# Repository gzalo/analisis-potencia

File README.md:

# Ataque a implementación embebida de AES-128 aplicando Analisis de Correlación de Potencia

Por Gonzalo Avila Alterach ([gzalo.com](https://gzalo.com))

Trabajo presentado en el SASE 2017: [Poster resumen](https://drive.google.com/file/d/0B66P5yRqMPOtamxIRzJjNnZKbFN4UW5kdmpBaS1vaHlMY0hv/view?usp=sharing&resourcekey=0-a8aOC6rB0S7HgKkPsgE3aA) y [Paper (en la página 176)](https://drive.google.com/file/d/0B66P5yRqMPOtMDNuS2NmNnpoXzQ/view?usp=sharing&resourcekey=0-7ZjvjVjSThMPrzhqmmbE-w)

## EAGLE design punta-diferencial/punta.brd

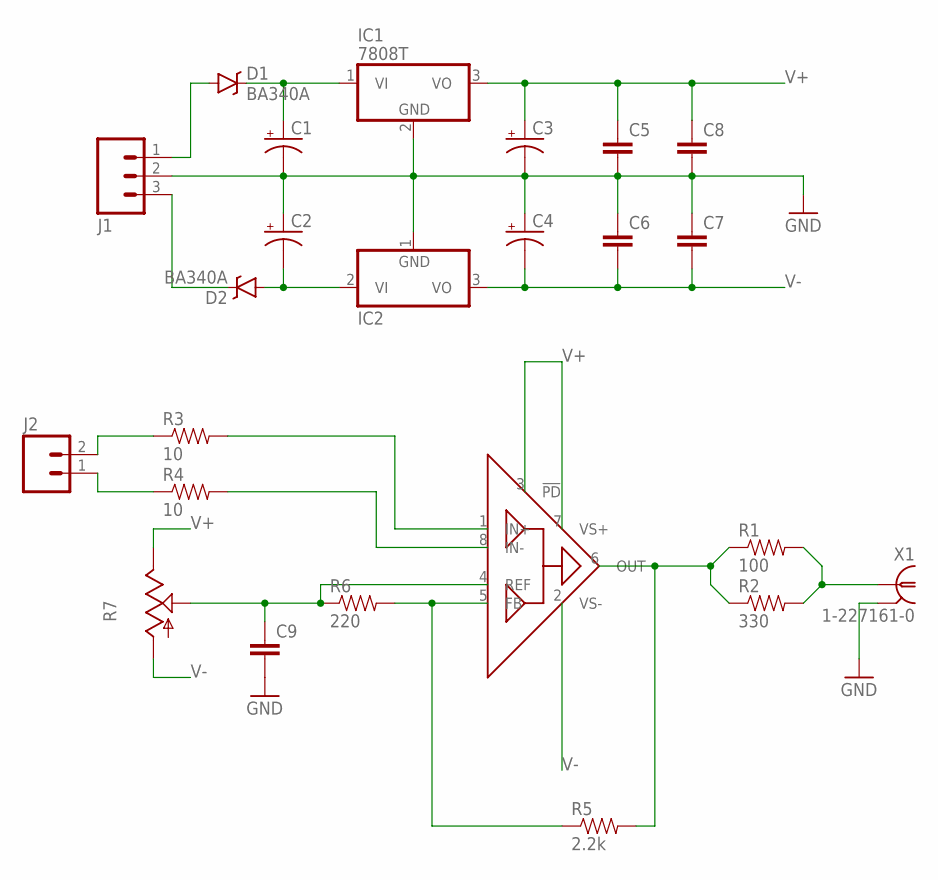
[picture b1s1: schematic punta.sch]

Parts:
C1, C2, C3, C4: CAP_POL1206-KIT; EIA3216-KIT
C5, C6, C7, C8, C9: CAP0805; 0805
D1, D2: BA340A; SMA-DIODE
IC1: 7808T; TO220H
IC2: 7908T; TO220H
J1: M03-SCREW-5MM; SCREWTERMINAL-5MM-3
J2: M02PTH; 1X02
R1: 100; 0805
R2: 330; 0805
R3, R4: 10; 0805
R5: 2.2k; 0805
R6: 220; 0805
R7: TRIM_US-B64Y; B64Y
U$1: AD8129ARZ; SOIC8
X1: 1-227161-0; AMP_227161

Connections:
GND: C1.C (-), C2.A (+), C3.C (-), C4.A (+), C5.2, C6.1, C7.1, C8.2, C9.2, IC1.2 (GND), IC2.1 (GND), J1.2, X1.2
unnamed: D1.A, J1.1
unnamed: C1.A (+), D1.C, IC1.1 (VI)
unnamed: R1.1, R2.1, R5.2, U$1.6 (OUT)
unnamed: C2.C (-), D2.A, IC2.2 (VI)
unnamed: D2.C, J1.3
unnamed: R1.2, R2.2, X1.1
unnamed: R3.2, U$1.1 (IN+)
unnamed: R4.2, U$1.8 (IN-)
unnamed: J2.2, R3.1
unnamed: J2.1, R4.1
unnamed: R5.1, R6.2, U$1.5 (FB)
unnamed: C9.1, R6.1, R7.S, U$1.4 (REF)
V+: C3.A (+), C5.1, C8.1, IC1.3 (VO), R7.E, U$1.3 (!PD), U$1.7 (VS+)
V-: C4.C (-), C6.2, C7.2, IC2.3 (VO), R7.A, U$1.2 (VS-)

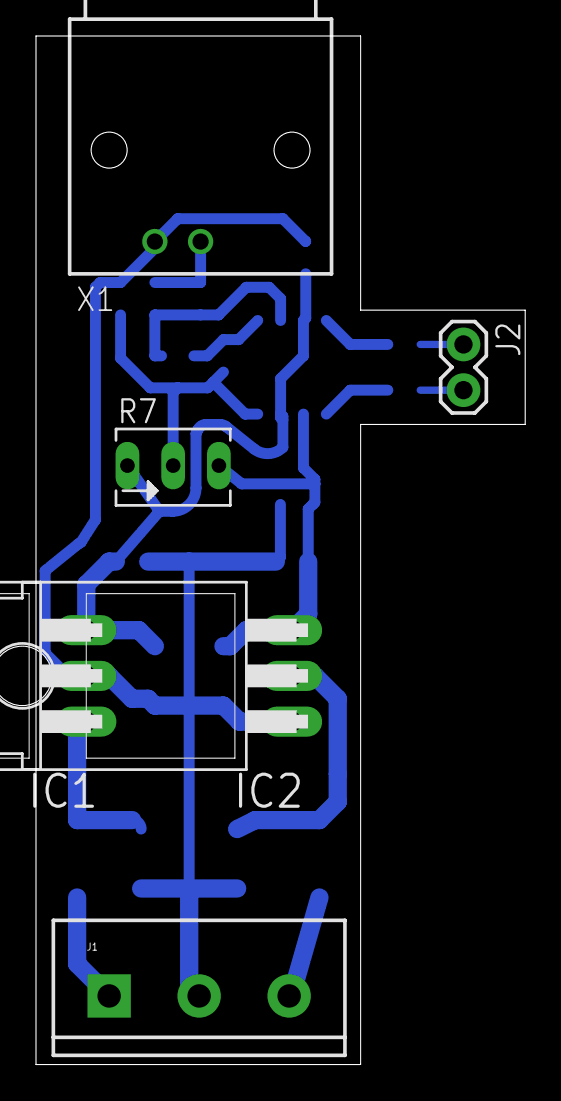
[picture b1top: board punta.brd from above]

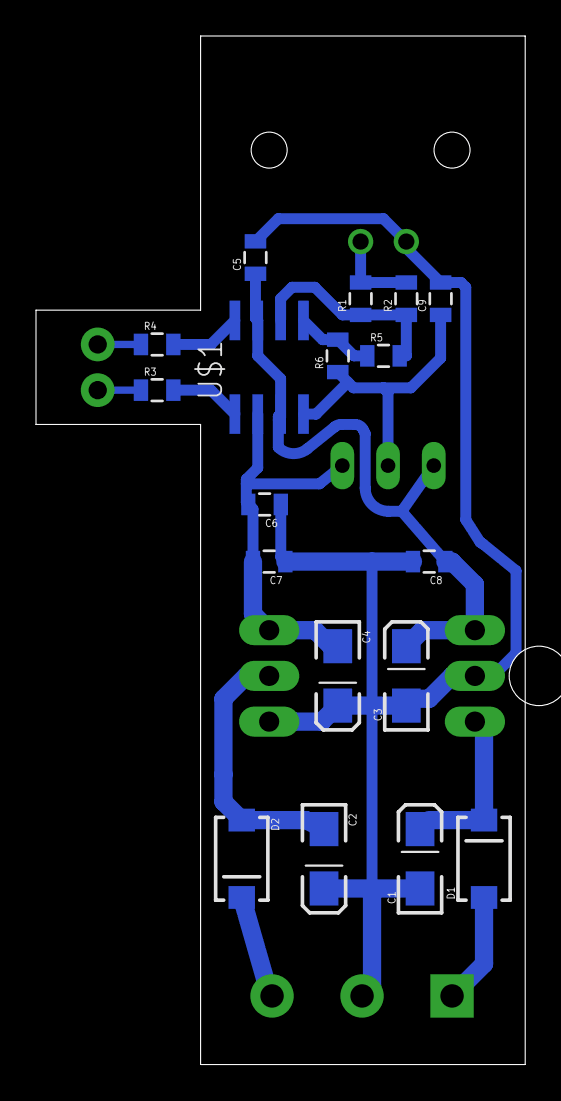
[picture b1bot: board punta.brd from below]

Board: 2 copper layers, 27.2 x 57.1 mm, 24 parts (18 on the bottom side), 15 nets.

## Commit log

2017-05-04 Agregado esquemático de plataforma con atxmega
2017-05-04 Agregado de firmware de prueba con aes128
2017-05-05 Agregado de punta diferencial
2017-05-05 Agregado readme con link a trabajo
2017-05-06 Add software

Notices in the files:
parts and their libraries:
SparkFun-Capacitors: Licensing: Creative Commons ShareAlike 4.0 International - https://creativecommons.org/licenses/by-sa/4.0
